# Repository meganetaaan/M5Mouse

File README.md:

# M5Mouse

A micro mouse PCB module & Software for M5Stack.

## Documents

Assembly and proguramming instructions are documented in the blog series "ししかわのマウス研修（Sskw's micro mouse training）"

- [Japanese](https://rt-net.jp/mobility/archives/9589#toc2)
- [English (auto translate)](https://1-rt--net-jp.translate.goog/mobility/archives/9589?_x_tr_enc=1&_x_tr_sl=ja&_x_tr_tl=en&_x_tr_hl=en-US&_x_tr_pto=nui#toc2)

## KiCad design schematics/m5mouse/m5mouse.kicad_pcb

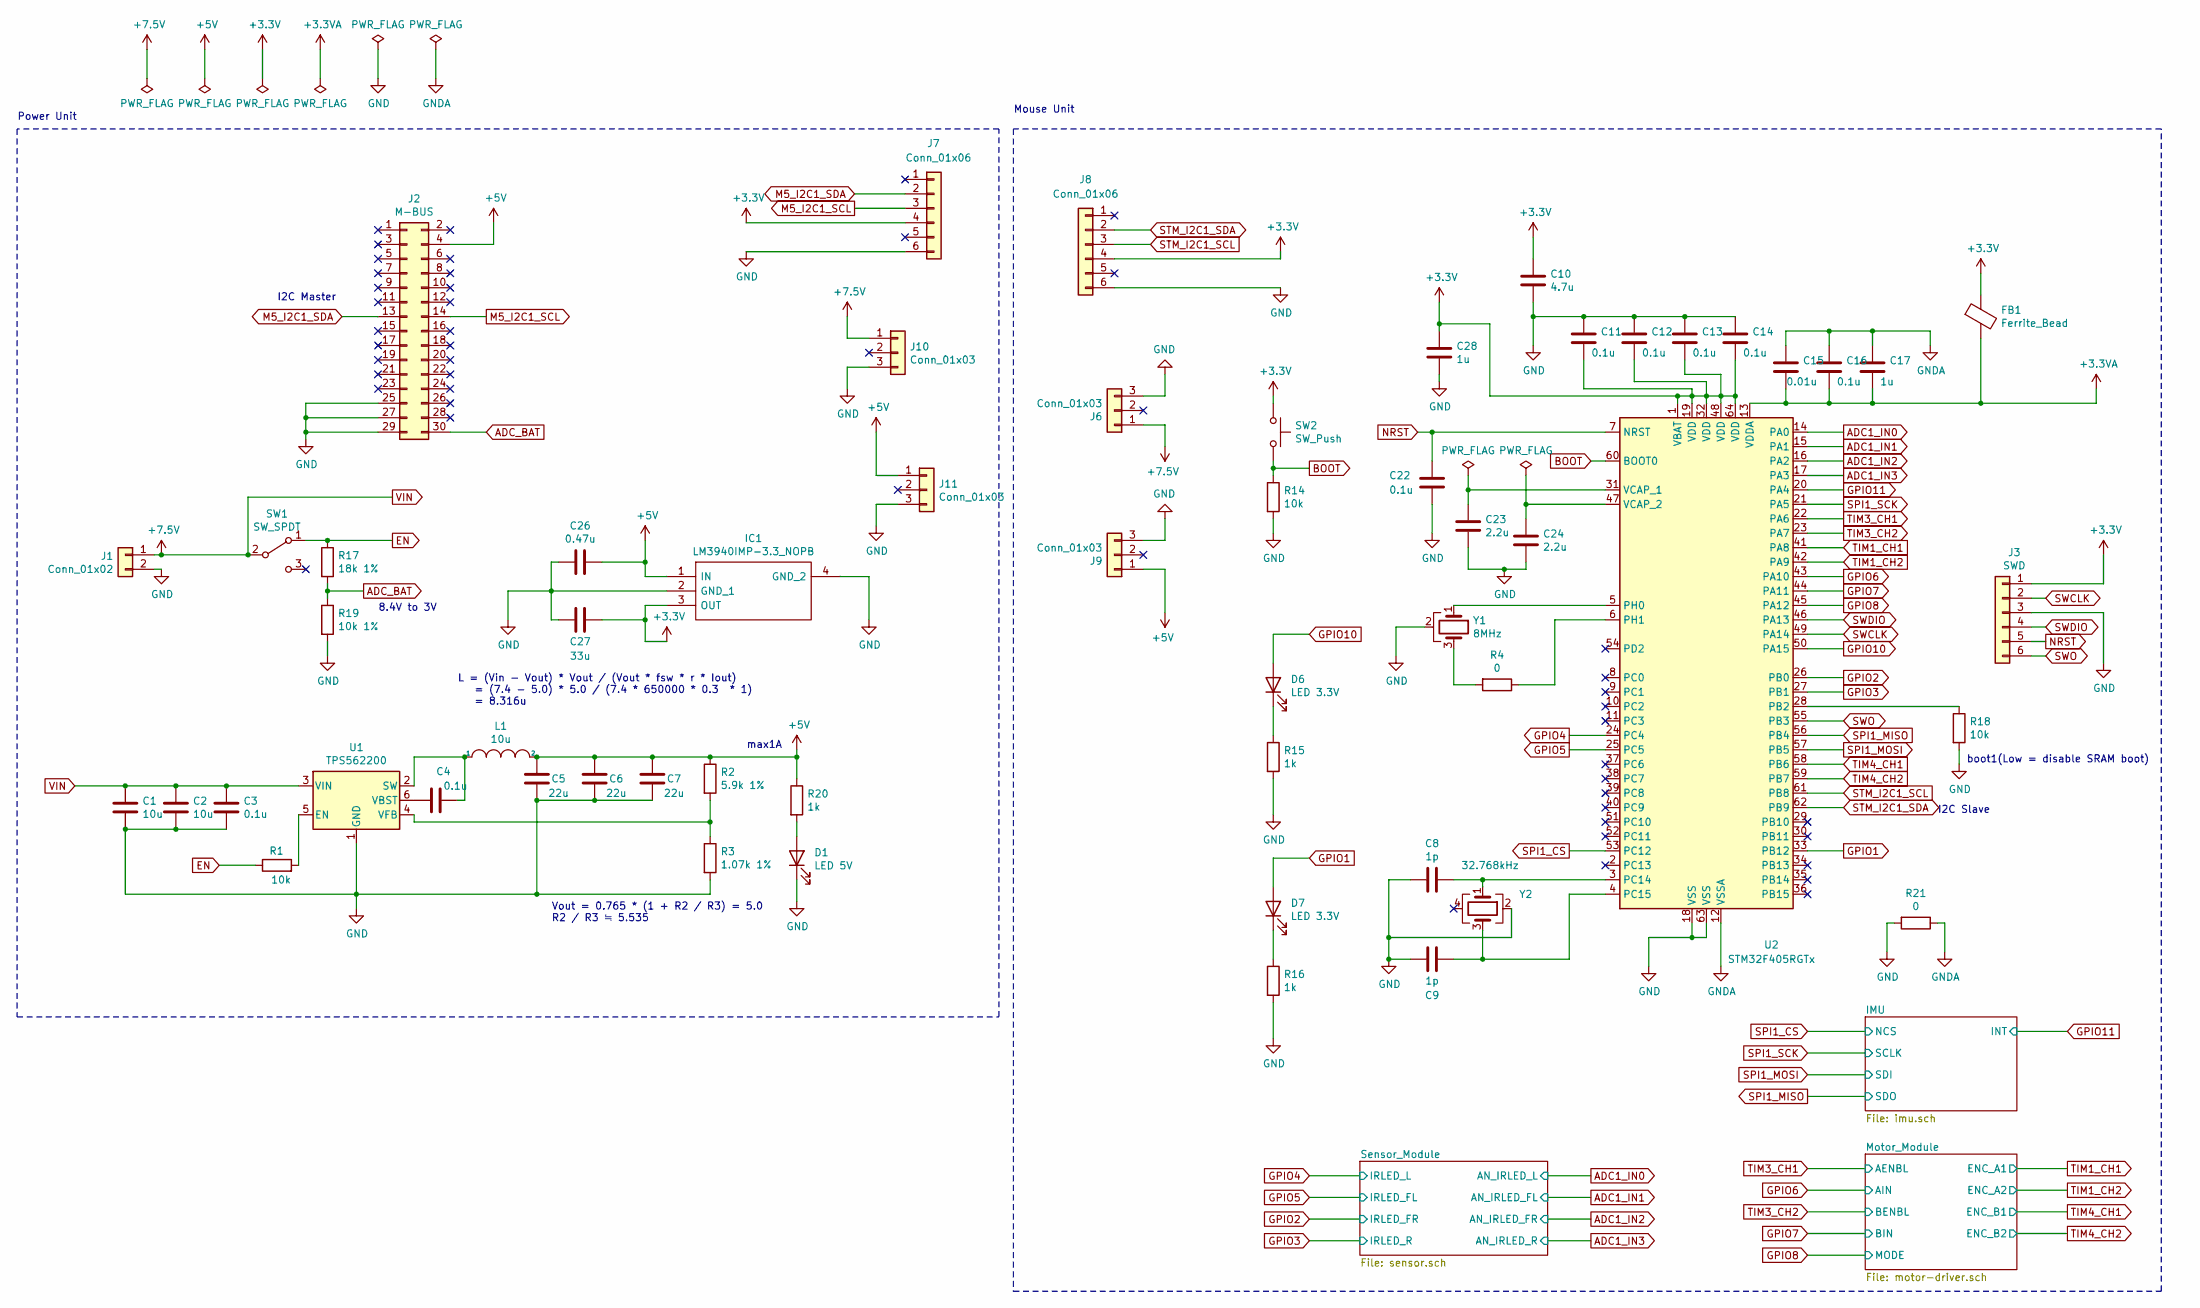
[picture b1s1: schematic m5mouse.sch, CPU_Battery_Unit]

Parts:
C1, C2: 10u; C_0603_1608Metric
C3, C4, C11, C12, C13, C14, C16, C22: 0.1u; C_0402_1005Metric
C5, C6, C7: 22u; C_0805_2012Metric
C8, C9: 1p; C_0201_0603Metric
C10: 4.7u; C_0402_1005Metric
C15: 0.01u; C_0402_1005Metric
C17, C28: 1u; C_0402_1005Metric
C23, C24: 2.2u; C_0402_1005Metric
C26: 0.47u; C_0402_1005Metric
C27: 33u; C_1206_3216Metric
D1: LED 5V; LED_D3.0mm_Horizontal_O1.27mm_Z2.0mm
D6, D7: LED 3.3V; LED_0603_1608Metric
FB1: Ferrite_Bead; R_0603_1608Metric
IC1: LM3940IMP-3.3_NOPB; LM3940IMP-3.3NOPB; Mouser Part Number 926-LM3940IMP3.3NOPB
J1: Conn_01x02; JST_PH_S2B-PH-K_1x02_P2.00mm_Horizontal
J2: M-BUS; PinHeader_2x15_P2.54mm_Vertical_SMD
J3: SWD; JST_EH_S6B-EH_1x06_P2.50mm_Horizontal
J6, J9: Conn_01x03; PinHeader_1x03_P2.54mm_Vertical
J7: Conn_01x06; PinSocket_1x06_P2.54mm_Vertical
J8: Conn_01x06; PinHeader_1x06_P2.54mm_Vertical
J10, J11: Conn_01x03; PinSocket_1x03_P2.54mm_Vertical
L1: 10u; L_1008_2520Metric
R1, R14, R18: 10k; R_0603_1608Metric
R2: 5.9k 1%; R_0603_1608Metric
R3: 1.07k 1%; R_0603_1608Metric
R4: 0; R_0603_1608Metric
R15, R16, R20: 1k; R_0603_1608Metric
R17: 18k 1%; R_0603_1608Metric
R19: 10k 1%; R_0603_1608Metric
R21: 0; R_0603_1608Metric_Pad1.05x0.95mm_HandSolder
SW1: SW_SPDT; SW_CuK_OS102011MA1QN1_SPDT_Angled
SW2: SW_Push; SW_Tactile_SPST_Angled_PTS645Vx39-2LFS
U1: TPS562200; SOT-23-6
U2: STM32F405RGTx; LQFP-64_10x10mm_P0.5mm
Y1: 8MHz; CSTNE8M00G55Z000R0
Y2: 32.768kHz; WMRAG32K76CS3C00R0

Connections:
+3.3VA: C15.2, C16.2, C17.2, FB1.2, U2.13 (VDDA); also elsewhere on the board
+3V3: C10.1, C11.2, C12.2, C13.2, C14.2, C27.1, C28.1, FB1.1, IC1.3 (OUT), J3.1, J7.4, J8.4, SW2.1, U2.1 (VBAT), U2.19 (VDD), U2.32 (VDD), U2.48 (VDD), U2.64 (VDD); also elsewhere on the board
+5V: C5.2, C6.2, C7.2, C26.1, IC1.1 (IN), J2.4, J9.1, J11.1, L1.2, R2.1, R20.1; also elsewhere on the board
ADC1_IN0: U2.14 (PA0); also elsewhere on the board
ADC1_IN1: U2.15 (PA1); also elsewhere on the board
ADC1_IN2: U2.16 (PA2); also elsewhere on the board
ADC1_IN3: U2.17 (PA3); also elsewhere on the board
ADC_BAT: J2.30, R17.2, R19.1
BOOT: R14.1, SW2.2, U2.60 (BOOT0)
EN: R1.1, R17.1, SW1.1 (A)
GND: C1.2, C2.2, C3.2, C5.1, C6.1, C7.1, C8.2, C9.2, C10.2, C11.1, C12.1, C13.1, C14.1, C22.2, C23.2, C24.2, C26.2, C27.2, C28.2, D1.1 (K), IC1.2 (GND_1), IC1.4 (GND_2), J1.2, J2.25, J2.27, J2.29, J3.3, J6.3, J7.6, J8.6, J9.3, J10.3, J11.3, R3.2, R14.2, R15.2, R16.2, R18.2, R19.2, R21.2, U1.1 (GND), U2.18 (VSS), U2.63 (VSS), Y1.2, Y2.2; also elsewhere on the board
GNDA: C15.1, C16.1, C17.1, R21.1, U2.12 (VSSA); also elsewhere on the board
GPIO1: D7.2 (A), U2.33 (PB12)
GPIO2: U2.26 (PB0); also elsewhere on the board
GPIO3: U2.27 (PB1); also elsewhere on the board
GPIO4: U2.24 (PC4); also elsewhere on the board
GPIO5: U2.25 (PC5); also elsewhere on the board
GPIO6: U2.43 (PA10); also elsewhere on the board
GPIO7: U2.44 (PA11); also elsewhere on the board
GPIO8: U2.45 (PA12); also elsewhere on the board
GPIO10: D6.2 (A), U2.50 (PA15)
GPIO11: U2.20 (PA4); also elsewhere on the board
M5_I2C1_SCL: J2.14, J7.3
M5_I2C1_SDA: J2.13, J7.2
NRST: C22.1, J3.5, U2.7 (NRST)
unnamed: C4.1, L1.1, U1.2 (SW)
unnamed: C4.2, U1.6 (VBST)
unnamed: C8.1, U2.3 (PC14), Y2.1
unnamed: C9.1, U2.4 (PC15), Y2.3
unnamed: C23.1, U2.31 (VCAP_1)
unnamed: C24.1, U2.47 (VCAP_2)
unnamed: D1.2 (A), R20.2
unnamed: D6.1 (K), R15.1
unnamed: D7.1 (K), R16.1
unnamed: R1.2, U1.5 (EN)
unnamed: R2.2, R3.1, U1.4 (VFB)
unnamed: R4.1, U2.6 (PH1)
unnamed: R4.2, Y1.3
unnamed: R18.1, U2.28 (PB2)
unnamed: U2.5 (PH0), Y1.1
SPI1_CS: U2.53 (PC12); also elsewhere on the board
SPI1_MISO: U2.56 (PB4); also elsewhere on the board
SPI1_MOSI: U2.57 (PB5); also elsewhere on the board
SPI1_SCK: U2.21 (PA5); also elsewhere on the board
STM_I2C1_SCL: J8.3, U2.61 (PB8)
STM_I2C1_SDA: J8.2, U2.62 (PB9)
SWCLK: J3.2, U2.49 (PA14)
SWDIO: J3.4, U2.46 (PA13)
SWO: J3.6, U2.55 (PB3)
TIM1_CH1: U2.41 (PA8); also elsewhere on the board
TIM1_CH2: U2.42 (PA9); also elsewhere on the board
TIM3_CH1: U2.22 (PA6); also elsewhere on the board
TIM3_CH2: U2.23 (PA7); also elsewhere on the board
TIM4_CH1: U2.58 (PB6); also elsewhere on the board
TIM4_CH2: U2.59 (PB7); also elsewhere on the board
VIN: C1.1, C2.1, C3.1, J1.1, J6.1, J10.1, SW1.2 (B), U1.3 (VIN); also elsewhere on the board

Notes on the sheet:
I2C Slave
I2C Master
Power Unit
Mouse Unit
L = (Vin - Vout) * Vout / (Vout * fsw * r * Iout) = (7.4 - 5.0) * 5.0 / (7.4 * 650000 * 0.3 * 1) = 8.316u
max1A
boot1(Low = disable SRAM boot)
Vout = 0.765 * (1 + R2 / R3) = 5.0 R2 / R3 ≒ 5.535
8.4V to 3V

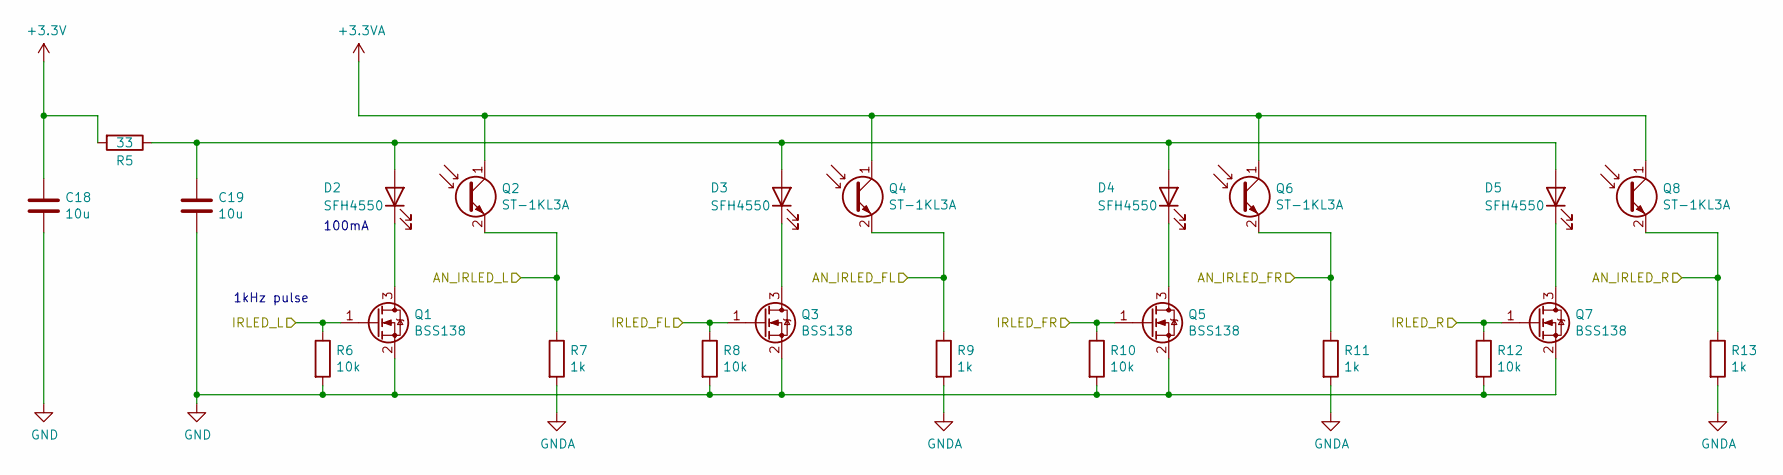
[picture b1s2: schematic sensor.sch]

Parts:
C18, C19: 10u; C_0402_1005Metric
D2, D3, D4, D5: SFH4550; ThroughHole_1x02_P2.54_Vertical
Q1, Q3, Q5, Q7: BSS138; SOT-23
Q2, Q4, Q6, Q8: ST-1KL3A; ThroughHole_1x02_P2.54_Vertical
R5: 33; R_0603_1608Metric
R6, R8, R10, R12: 10k; R_0603_1608Metric
R7, R9, R11, R13: 1k; R_0603_1608Metric

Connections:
+3.3VA: Q2.1 (C), Q4.1 (C), Q6.1 (C), Q8.1 (C); also elsewhere on the board
+3V3: C18.1, R5.2; also elsewhere on the board
ADC1_IN0: Q2.2 (E), R7.1; also elsewhere on the board
ADC1_IN1: Q4.2 (E), R9.1; also elsewhere on the board
ADC1_IN2: Q6.2 (E), R11.1; also elsewhere on the board
ADC1_IN3: Q8.2 (E), R13.1; also elsewhere on the board
GND: C18.2, C19.2, Q1.2 (S), Q3.2 (S), Q5.2 (S), Q7.2 (S), R6.2, R8.2, R10.2, R12.2; also elsewhere on the board
GNDA: R7.2, R9.2, R11.2, R13.2; also elsewhere on the board
GPIO2: Q5.1 (G), R10.1; also elsewhere on the board
GPIO3: Q7.1 (G), R12.1; also elsewhere on the board
GPIO4: Q1.1 (G), R6.1; also elsewhere on the board
GPIO5: Q3.1 (G), R8.1; also elsewhere on the board
unnamed: C19.1, D2.2 (A), D3.2 (A), D4.2 (A), D5.2 (A), R5.1
unnamed: D2.1 (K), Q1.3 (D)
unnamed: D3.1 (K), Q3.3 (D)
unnamed: D4.1 (K), Q5.3 (D)
unnamed: D5.1 (K), Q7.3 (D)

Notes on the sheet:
1kHz pulse
100mA

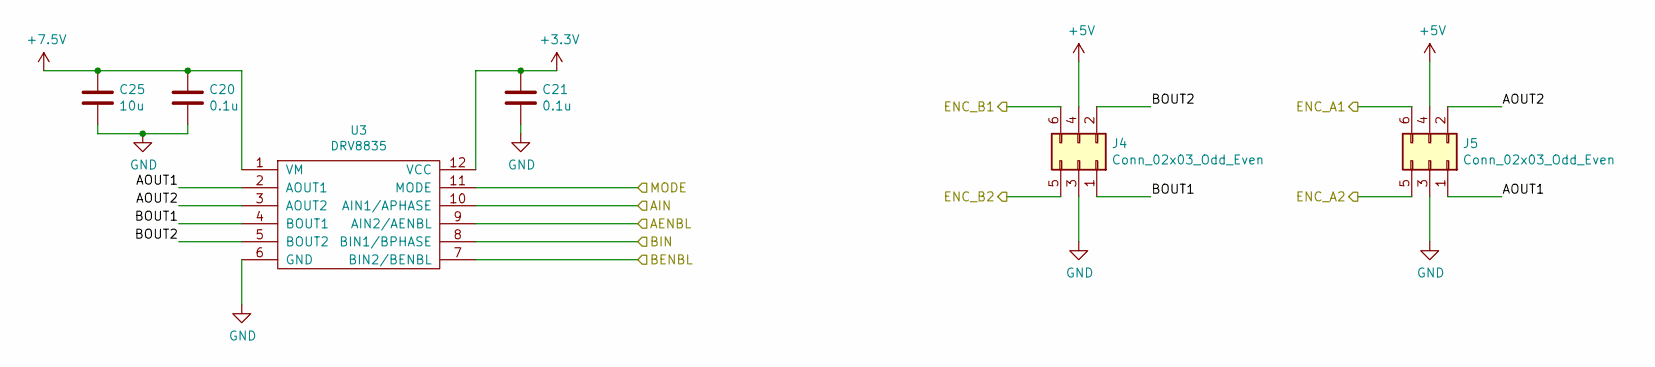
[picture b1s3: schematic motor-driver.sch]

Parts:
C20, C21: 0.1u; C_0402_1005Metric
C25: 10u; C_0402_1005Metric
J4, J5: Conn_02x03_Odd_Even; PinHeader_2x03_P2.54mm_Vertical
U3: DRV8835; WSON-12-1EP_3x2mm_P0.5mm_EP1x2.65

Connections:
+3V3: C21.1, U3.12 (VCC); also elsewhere on the board
+5V: J4.4, J5.4; also elsewhere on the board
/Motor_Module/AOUT1: J5.1, U3.2 (AOUT1)
/Motor_Module/AOUT2: J5.2, U3.3 (AOUT2)
/Motor_Module/BOUT1: J4.1, U3.4 (BOUT1)
/Motor_Module/BOUT2: J4.2, U3.5 (BOUT2)
GND: C20.2, C21.2, C25.2, J4.3, J5.3, U3.6 (GND), U3.13; also elsewhere on the board
GPIO6: U3.10 (AIN1/APHASE); also elsewhere on the board
GPIO7: U3.8 (BIN1/BPHASE); also elsewhere on the board
GPIO8: U3.11 (MODE); also elsewhere on the board
TIM1_CH1: J5.6; also elsewhere on the board
TIM1_CH2: J5.5; also elsewhere on the board
TIM3_CH1: U3.9 (AIN2/AENBL); also elsewhere on the board
TIM3_CH2: U3.7 (BIN2/BENBL); also elsewhere on the board
TIM4_CH1: J4.6; also elsewhere on the board
TIM4_CH2: J4.5; also elsewhere on the board
VIN: C20.1, C25.1, U3.1 (VM); also elsewhere on the board

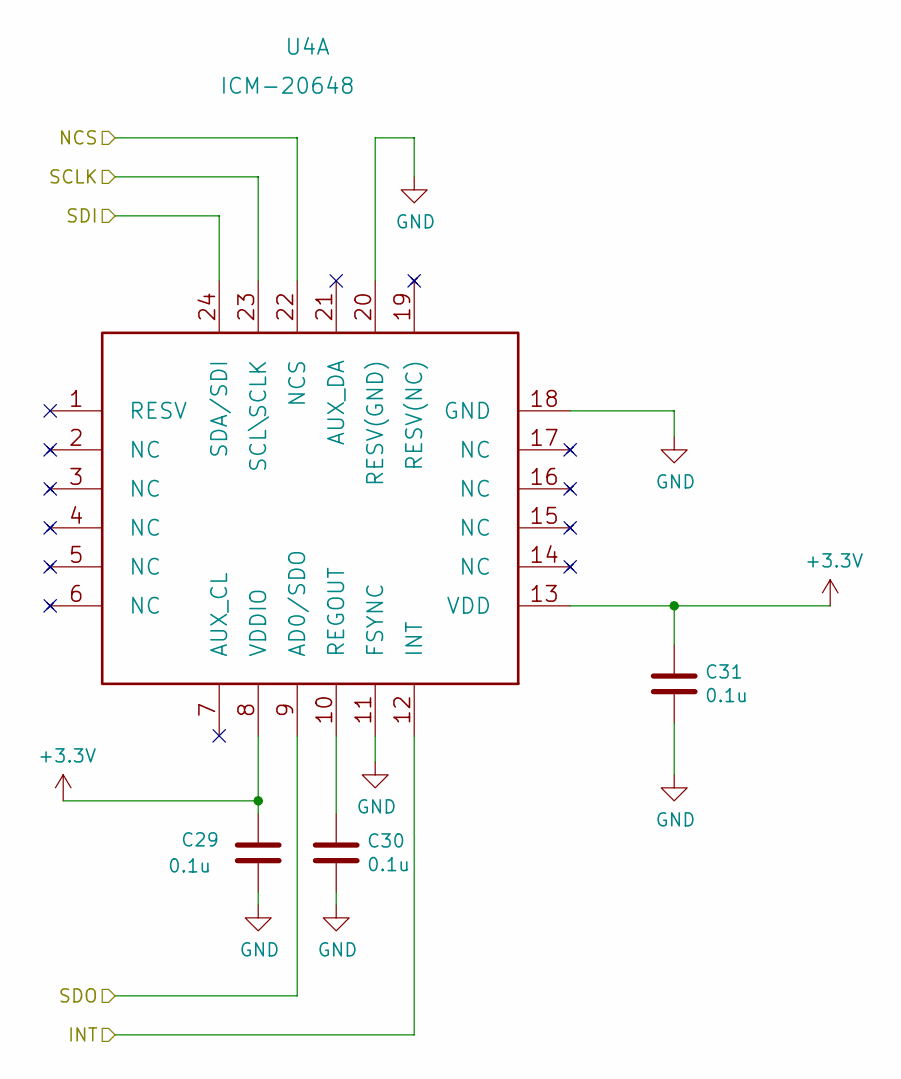
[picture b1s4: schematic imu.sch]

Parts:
C29, C30, C31: 0.1u; C_0402_1005Metric
U4: ICM-20648; QFN-24-1EP_3x3mm_P0.4mm_EP1.75x1.6mm

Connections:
+3V3: C29.1, C31.1, U4.8 (VDDIO), U4.13 (VDD); also elsewhere on the board
GND: C29.2, C30.2, C31.2, U4.11 (FSYNC), U4.18 (GND), U4.20 (RESV(GND)); also elsewhere on the board
GPIO11: U4.12 (INT); also elsewhere on the board
unnamed: C30.1, U4.10 (REGOUT)
SPI1_CS: U4.22 (NCS); also elsewhere on the board
SPI1_MISO: U4.9 (AD0/SDO); also elsewhere on the board
SPI1_MOSI: U4.24 (SDA/SDI); also elsewhere on the board
SPI1_SCK: U4.23 (SCL\SCLK); also elsewhere on the board

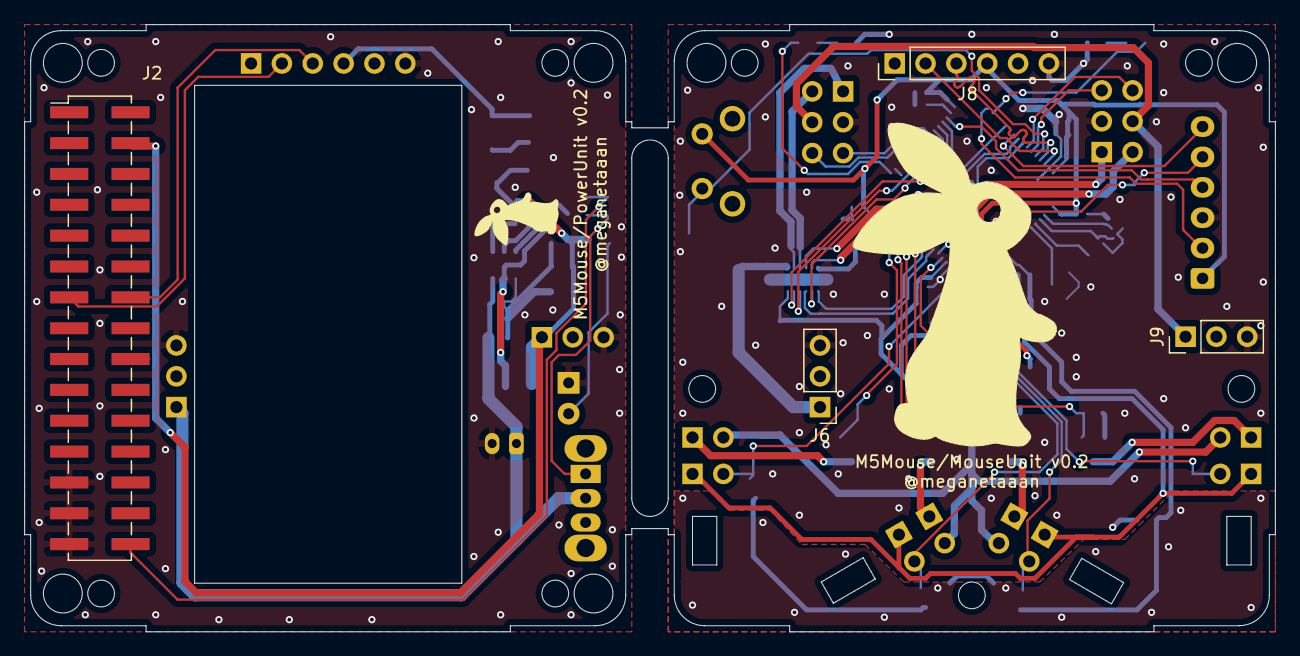
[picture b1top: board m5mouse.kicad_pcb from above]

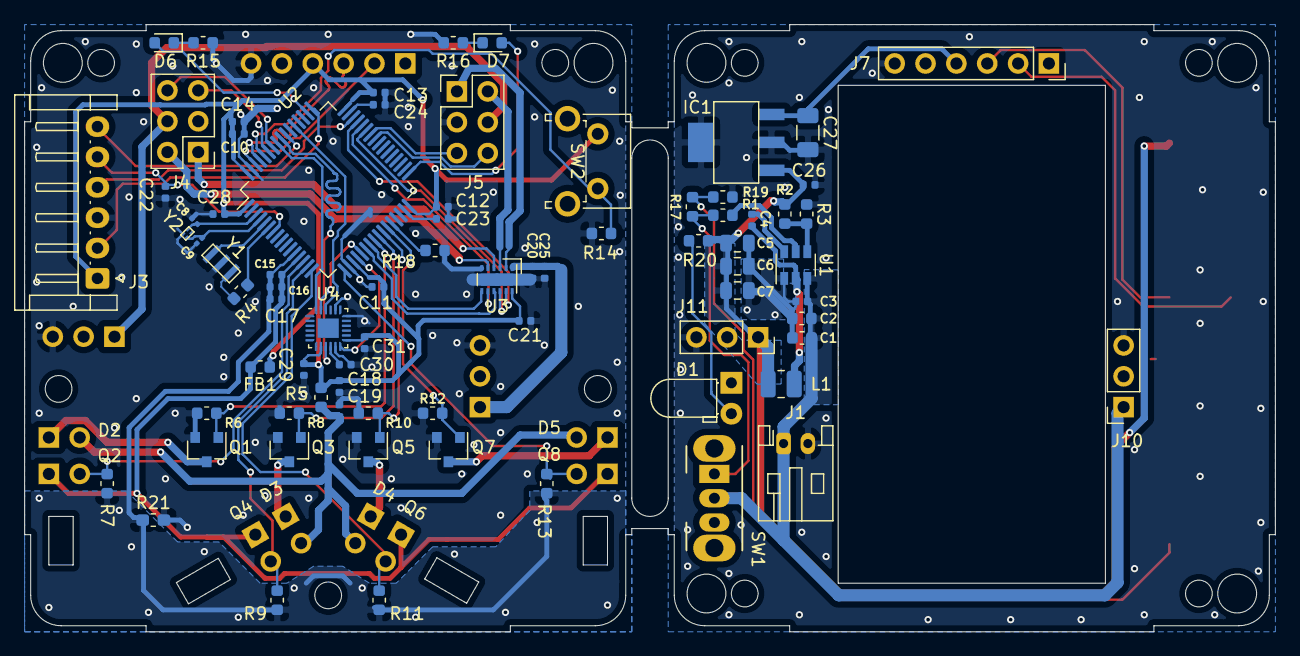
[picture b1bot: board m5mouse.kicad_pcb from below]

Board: 2 copper layers, 103.0 x 50.0 mm, 98 parts (85 on the bottom side), 66 nets.

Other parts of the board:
MH1, MH2, MH3, MH4, MH5, MH8: mountinghole_M2_M3
MH6, MH7, MH10: MountingHole_2.2mm_M2

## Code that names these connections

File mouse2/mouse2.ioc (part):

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Mcu.Name=STM32F405RGTx
Mcu.Package=LQFP64
Mcu.UserName=STM32F405RGTx
PA0-WKUP.Signal=ADCx_IN0
PA1.Signal=ADCx_IN1
PA10.Signal=GPIO_Output
PA11.Signal=GPIO_Output
PA12.Signal=GPIO_Output
PA13.Mode=Trace_Asynchronous_SW
PA13.Signal=SYS_JTMS-SWDIO
PA14.Mode=Trace_Asynchronous_SW
PA14.Signal=SYS_JTCK-SWCLK
PA15.Signal=GPIO_Output
PA2.Signal=ADCx_IN2
PA3.Signal=ADCx_IN3
PA4.Signal=GPIO_Input
PA5.Mode=Full_Duplex_Master
PA5.Signal=SPI1_SCK
PA6.Signal=S_TIM3_CH1
PA7.Signal=S_TIM3_CH2
PA8.Signal=S_TIM1_CH1
PA9.Signal=S_TIM1_CH2
PB0.Signal=GPIO_Output
PB1.Signal=GPIO_Output
PB10.Mode=Asynchronous
PB10.Signal=USART3_TX
PB11.Mode=Asynchronous
PB11.Signal=USART3_RX
PB12.Signal=GPIO_Output
PB3.Mode=Trace_Asynchronous_SW
PB3.Signal=SYS_JTDO-SWO
PB4.Mode=Full_Duplex_Master
PB4.Signal=SPI1_MISO
PB5.Mode=Full_Duplex_Master
PB5.Signal=SPI1_MOSI
PB6.Signal=S_TIM4_CH1
PB7.Signal=S_TIM4_CH2
PB8.Mode=I2C
PB8.Signal=I2C1_SCL
PB9.Mode=I2C
PB9.Signal=I2C1_SDA
PC12.Signal=GPIO_Output
PC14-OSC32_IN.Mode=LSE-External-Oscillator
PC14-OSC32_IN.Signal=RCC_OSC32_IN
PC15-OSC32_OUT.Mode=LSE-External-Oscillator
PC15-OSC32_OUT.Signal=RCC_OSC32_OUT
PC4.Signal=GPIO_Output
PC5.Signal=GPIO_Output
PH0-OSC_IN.Mode=HSE-External-Oscillator
PH0-OSC_IN.Signal=RCC_OSC_IN
PH1-OSC_OUT.Mode=HSE-External-Oscillator
PH1-OSC_OUT.Signal=RCC_OSC_OUT
RCC.HSE_VALUE=8000000
RCC.SYSCLKFreq_VALUE=168000000
RCC.SYSCLKSource=RCC_SYSCLKSOURCE_PLLCLK
board=custom

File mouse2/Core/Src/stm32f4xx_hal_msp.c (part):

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  
    __HAL_RCC_GPIOA_CLK_ENABLE();
    /**ADC1 GPIO Configuration    
    PA0-WKUP     ------> ADC1_IN0
    PA1     ------> ADC1_IN1
    PA2     ------> ADC1_IN2
    PA3     ------> ADC1_IN3 
    */
    GPIO_InitStruct.Pin = GPIO_PIN_0|GPIO_PIN_1|GPIO_PIN_2|GPIO_PIN_3;
    GPIO_InitStruct.Mode = GPIO_MODE_ANALOG;
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    __HAL_RCC_ADC1_CLK_DISABLE();
  
    /**ADC1 GPIO Configuration    
    PA0-WKUP     ------> ADC1_IN0
    PA1     ------> ADC1_IN1
    PA2     ------> ADC1_IN2
    PA3     ------> ADC1_IN3 
    */
    HAL_GPIO_DeInit(GPIOA, GPIO_PIN_0|GPIO_PIN_1|GPIO_PIN_2|GPIO_PIN_3);

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  
    __HAL_RCC_GPIOB_CLK_ENABLE();
    /**I2C1 GPIO Configuration    
    PB8     ------> I2C1_SCL
    PB9     ------> I2C1_SDA 
    */
    GPIO_InitStruct.Pin = GPIO_PIN_8|GPIO_PIN_9;
    GPIO_InitStruct.Mode = GPIO_MODE_AF_OD;
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    __HAL_RCC_I2C1_CLK_DISABLE();
  
    /**I2C1 GPIO Configuration    
    PB8     ------> I2C1_SCL
    PB9     ------> I2C1_SDA 
    */
    HAL_GPIO_DeInit(GPIOB, GPIO_PIN_8|GPIO_PIN_9);

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    __HAL_RCC_GPIOA_CLK_ENABLE();
    __HAL_RCC_GPIOB_CLK_ENABLE();
    /**SPI1 GPIO Configuration    
    PA5     ------> SPI1_SCK
    PB4     ------> SPI1_MISO
    PB5     ------> SPI1_MOSI 
    */
    GPIO_InitStruct.Pin = GPIO_PIN_5;
    GPIO_InitStruct.Mode = GPIO_MODE_AF_PP;
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    __HAL_RCC_SPI1_CLK_DISABLE();
  
    /**SPI1 GPIO Configuration    
    PA5     ------> SPI1_SCK
    PB4     ------> SPI1_MISO
    PB5     ------> SPI1_MOSI 
    */
    HAL_GPIO_DeInit(GPIOA, GPIO_PIN_5);

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  
    __HAL_RCC_GPIOA_CLK_ENABLE();
    /**TIM1 GPIO Configuration    
    PA8     ------> TIM1_CH1
    PA9     ------> TIM1_CH2 
    */
    GPIO_InitStruct.Pin = GPIO_PIN_8|GPIO_PIN_9;
    GPIO_InitStruct.Mode = GPIO_MODE_AF_PP;
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  
    __HAL_RCC_GPIOB_CLK_ENABLE();
    /**TIM4 GPIO Configuration    
    PB6     ------> TIM4_CH1
    PB7     ------> TIM4_CH2 
    */
    GPIO_InitStruct.Pin = GPIO_PIN_6|GPIO_PIN_7;
    GPIO_InitStruct.Mode = GPIO_MODE_AF_PP;
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  
    __HAL_RCC_GPIOA_CLK_ENABLE();
    /**TIM3 GPIO Configuration    
    PA6     ------> TIM3_CH1
    PA7     ------> TIM3_CH2 
    */
    GPIO_InitStruct.Pin = GPIO_PIN_6|GPIO_PIN_7;
    GPIO_InitStruct.Mode = GPIO_MODE_AF_PP;
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    __HAL_RCC_TIM1_CLK_DISABLE();
  
    /**TIM1 GPIO Configuration    
    PA8     ------> TIM1_CH1
    PA9     ------> TIM1_CH2 
    */
    HAL_GPIO_DeInit(GPIOA, GPIO_PIN_8|GPIO_PIN_9);

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    __HAL_RCC_TIM4_CLK_DISABLE();
  
    /**TIM4 GPIO Configuration    
    PB6     ------> TIM4_CH1
    PB7     ------> TIM4_CH2 
    */
    HAL_GPIO_DeInit(GPIOB, GPIO_PIN_6|GPIO_PIN_7);

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
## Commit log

2020-02-06 Add launch settings
2020-02-14 Add I2C function
2020-02-26 Add PWM
2020-02-26 Add who-am-i communication via I2C
2020-02-26 Add VSCode configuration
2020-03-27 Fix Timer period
2020-06-19 WIP: Add schematics
2020-07-03 Add schematics
2020-07-06 schematic v0.1
2020-07-06 Add schematic image
2020-07-22 Fix schematics
2020-08-26 Put parts
2020-08-27 Adjust parts positions
2020-08-27 Draw pattern
2020-08-27 Fix path
2020-09-01 Connect GNDA and GND via ferrite bead
2020-09-01 Add gerber
2020-09-01 plot PDF
2020-09-02 Fix silk overlap
2020-09-08 Fix global label direction
2020-09-08 Fix path length
2020-09-09 Refactor pattern layout
2020-09-09 plot
2020-09-09 Fix patterns
2020-09-09 Fix pattern
2020-09-10 Fix part position and path
2020-09-10 Update gerber files
2020-09-18 Fix schematics and patterns
2020-09-24 Update m5mouse.kicad_pcb
    Fix parts position
2020-09-24 Fix parts position
2020-09-24 Change ferrite bead
2020-09-24 Generate gerber
2020-09-24 Generate step file
2020-09-29 Fix flipped pin header
2020-11-20 generate gerber files archive in script
2021-01-05 Generate mosue2 project
2021-01-05 carriage return
2021-01-05 Test adc
2021-01-14 Add drivers
2021-01-15 Add sensor driver
2021-01-15 WIP: Add controller
2021-01-18 Add pins/i2c
2021-01-18 Add mosue update
2021-01-18 Add pid update
2021-01-19 WIP: Add i2c
2021-01-19 WIP: set hispeed I2C
2021-01-21 WIP: implement driving sequence
2021-01-28 Add maze
2021-01-28 Fix connector
2021-01-28 blink led on hard fault
2021-01-28 Refactor
2021-01-28 Add agent
2021-01-29 Add simulation mode
2021-02-02 Add sensors
2021-02-02 Add wall adjuster
2021-02-03 Add calibrate command
2021-02-03 Make it goal
2021-02-04 Add sim
2021-02-04 WIP: refactor
2021-02-04 WIP: Add odometry
2021-02-05 Add slalom
2021-02-05 Improve stability
2021-02-08 Rename firmware
2021-02-08 Add startup sound
2021-02-08 Add wall adjustment
2021-02-08 Slalom for searching
2021-02-08 Refactor test methods
2021-02-08 Add test commands
2021-02-09 WIP: faster search
2021-02-09 WIP: fix
2021-02-09 WIP: Adjust gain
2021-02-09 Adjust gain
2021-04-02 Add class diagram
2021-04-12 Add diagrams
2021-05-07 Reprint PDF
2021-11-14 added BOM
2021-11-14 Added pick & place
    Generated from easyeda
2021-11-15 Added image and PDF of PCB
2021-11-15 Added image of pins used by M5 Mouse
2021-11-15 added image
2021-11-15 Added very very basic readme
2021-11-15 Fix image
    Fix image
2021-11-15 Added PCB image
2021-11-15 reorder
2021-11-16 Fix README

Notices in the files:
mouse2/Core/Src/stm32f4xx_hal_msp.c:
© Copyright (c) 2021 STMicroelectronics.
All rights reserved.
This software component is licensed by ST under BSD 3-Clause license,
the "License"; You may not use this file except in compliance with the
License. You may obtain a copy of the License at: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
(C) COPYRIGHT STMicroelectronics *****END OF FILE
